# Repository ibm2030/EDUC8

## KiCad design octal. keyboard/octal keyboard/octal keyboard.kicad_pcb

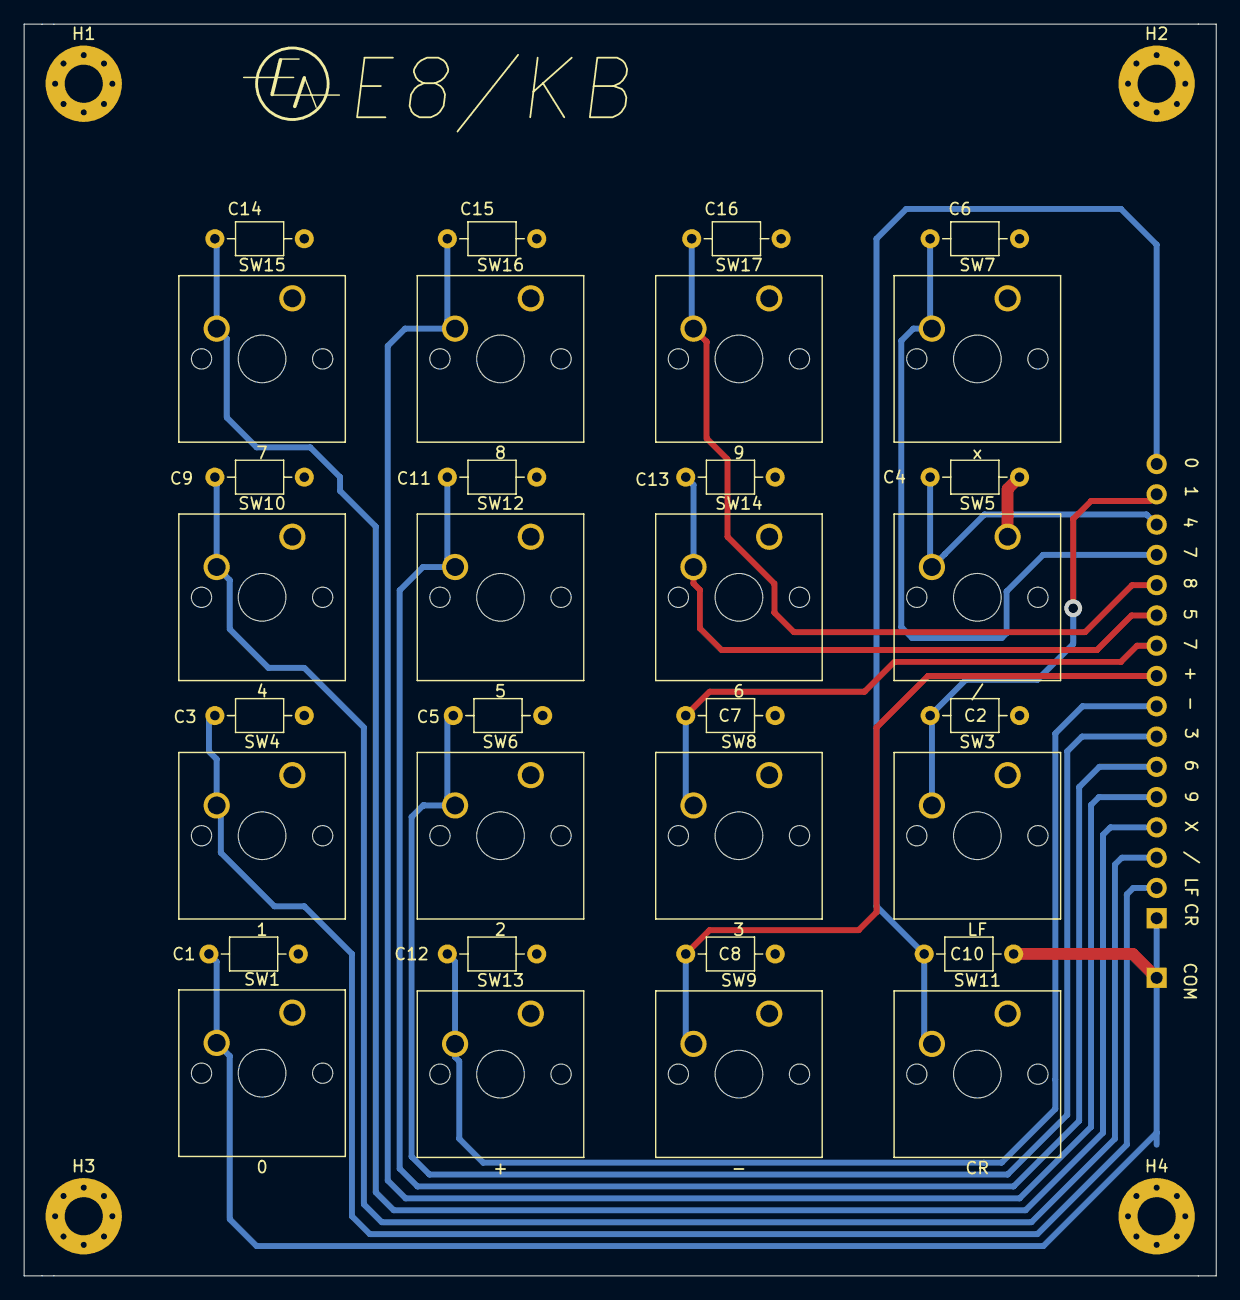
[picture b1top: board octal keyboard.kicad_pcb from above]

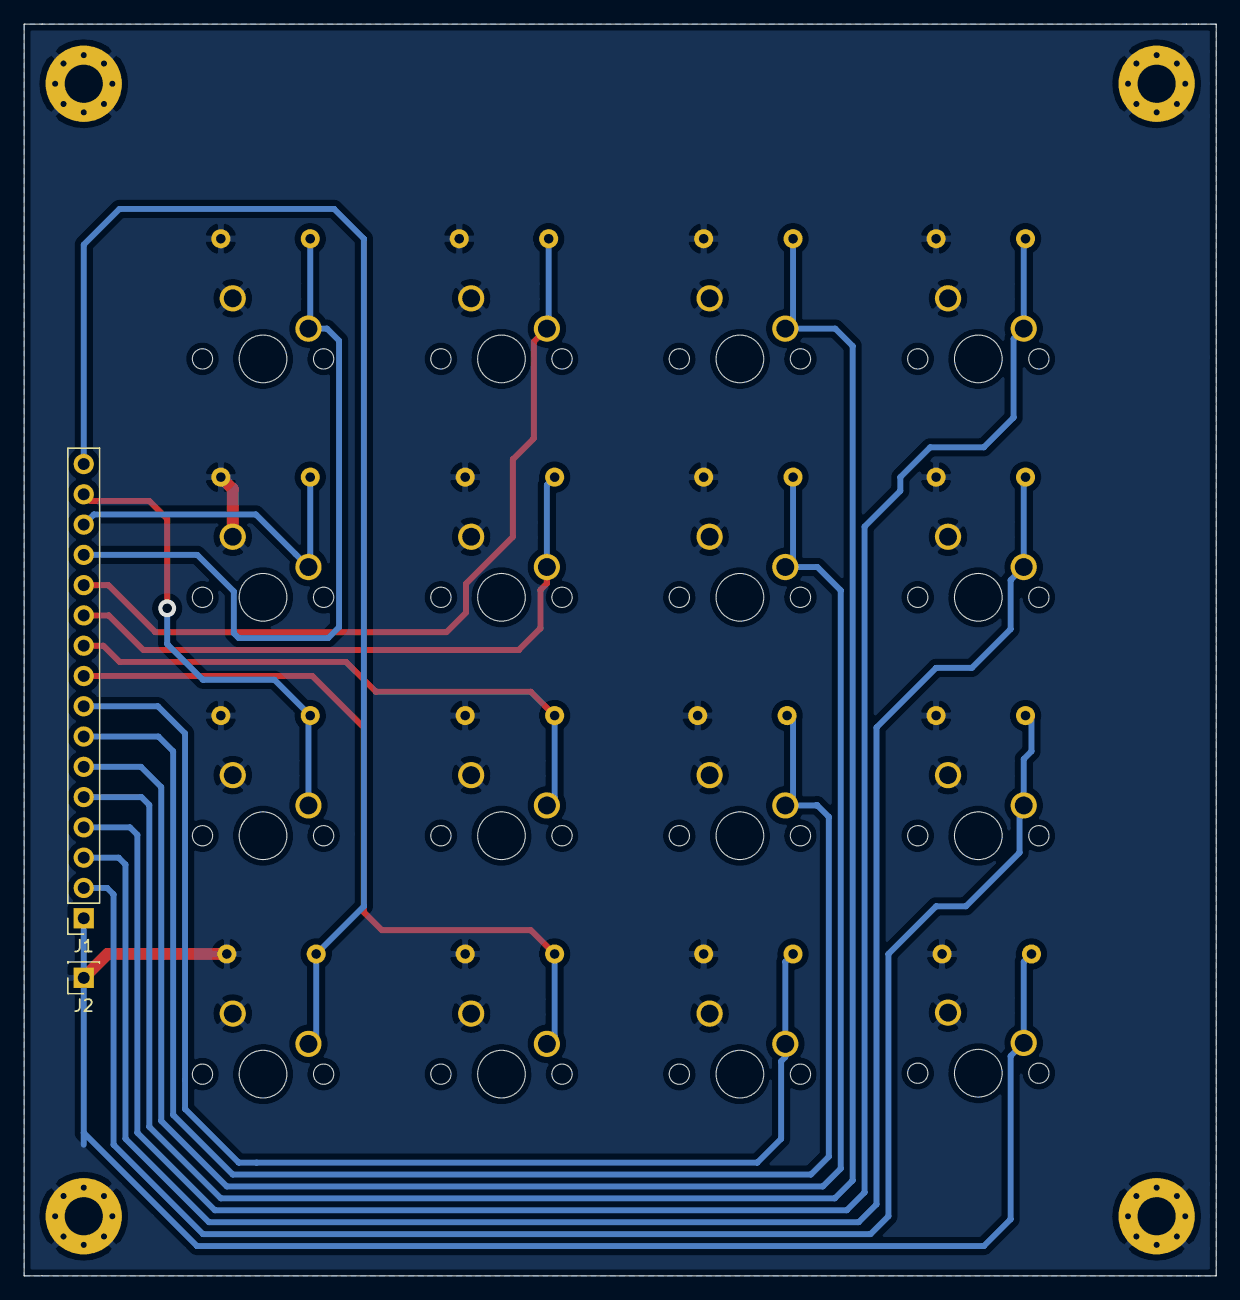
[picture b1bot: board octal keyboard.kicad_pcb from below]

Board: 2 copper layers, 100.0 x 105.0 mm, 38 parts (2 on the bottom side), 17 nets.

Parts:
C1, C3, C4, C5, C6, C7, C8, C9, C10, C11, C12, C13, C14, C15, C16: C_Small; C_Axial_L3.8mm_D2.6mm_P7.50mm_Horizontal
C2: 10nF; C_Axial_L3.8mm_D2.6mm_P7.50mm_Horizontal
H1, H2, H3, H4: MountingHole_Pad; MountingHole_3.2mm_M3_Pad_Via
J1: Conn_01x16_Male; PinSocket_1x16_P2.54mm_Vertical
J2: Conn_01x01_Female; PinSocket_1x01_P2.54mm_Vertical
SW1: 0; SW_Cherry_MX_1.00u_PCB
SW3: LF; SW_Cherry_MX_1.00u_PCB
SW4: 1; SW_Cherry_MX_1.00u_PCB
SW5: /; SW_Cherry_MX_1.00u_PCB
SW6: 2; SW_Cherry_MX_1.00u_PCB
SW7: x; SW_Cherry_MX_1.00u_PCB
SW8: 3; SW_Cherry_MX_1.00u_PCB
SW9: -; SW_Cherry_MX_1.00u_PCB
SW10: 4; SW_Cherry_MX_1.00u_PCB
SW11: CR; SW_Cherry_MX_1.00u_PCB
SW12: 5; SW_Cherry_MX_1.00u_PCB
SW13: +; SW_Cherry_MX_1.00u_PCB
SW14: 6; SW_Cherry_MX_1.00u_PCB
SW15: 7; SW_Cherry_MX_1.00u_PCB
SW16: 8; SW_Cherry_MX_1.00u_PCB
SW17: 9; SW_Cherry_MX_1.00u_PCB

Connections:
0: C1.1, J1.1, SW1.2
1: C3.1, J1.2, SW4.2
2: C5.1, J1.7, SW6.2
3: C7.1, J1.10, SW8.2
4: C9.1, J1.3, SW10.2
5: C11.1, J1.6, SW12.2
6: C13.1, J1.11, SW14.2
7: C14.1, J1.4, SW15.2
8: C15.1, J1.5, SW16.2
9: C16.1, J1.12, SW17.2
+: C12.1, J1.8, SW13.2
-: C8.1, J1.9, SW9.2
COM: C1.2, C2.2, C3.2, C4.2, C5.2, C6.2, C7.2, C8.2, C9.2, C10.2, C11.2, C12.2, C13.2, C14.2, C15.2, C16.2, H1.1, H2.1, H3.1, H4.1, J2.1, SW1.1, SW3.1, SW4.1, SW5.1, SW6.1, SW7.1, SW8.1, SW9.1, SW10.1, SW11.1, SW12.1, SW13.1, SW14.1, SW15.1, SW16.1, SW17.1
CR: C10.1, J1.16, SW11.2
DIV: C4.1, J1.14, SW5.2
LF: C2.1, J1.15, SW3.2
X: C6.1, J1.13, SW7.2

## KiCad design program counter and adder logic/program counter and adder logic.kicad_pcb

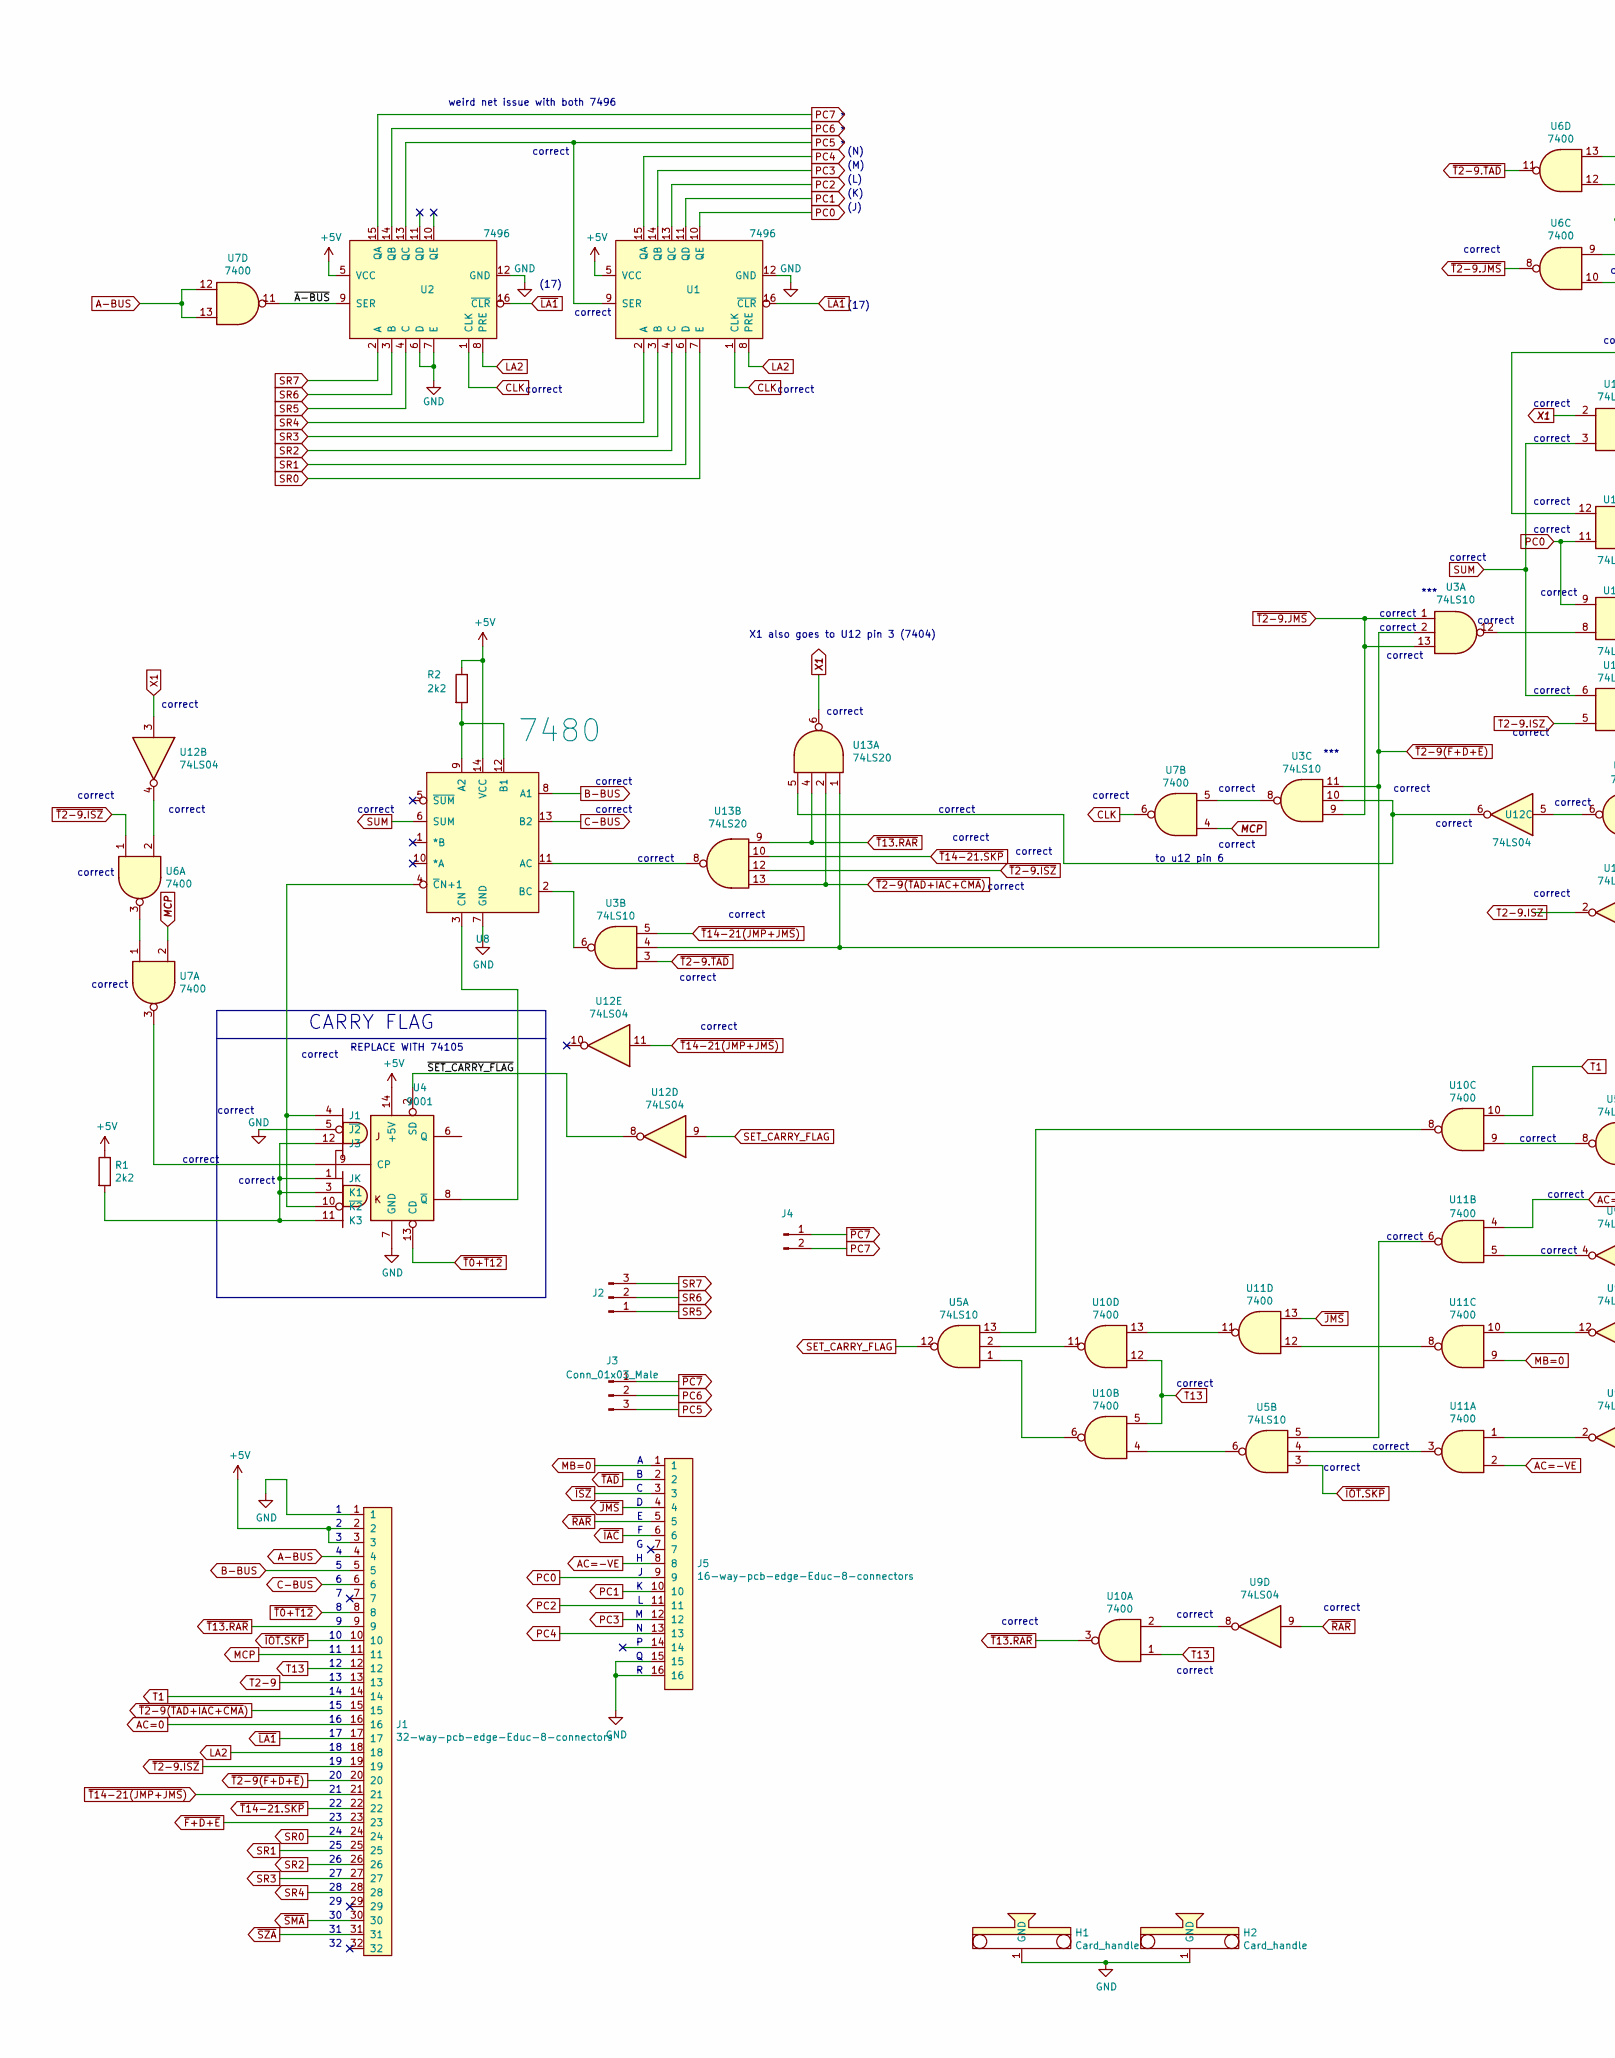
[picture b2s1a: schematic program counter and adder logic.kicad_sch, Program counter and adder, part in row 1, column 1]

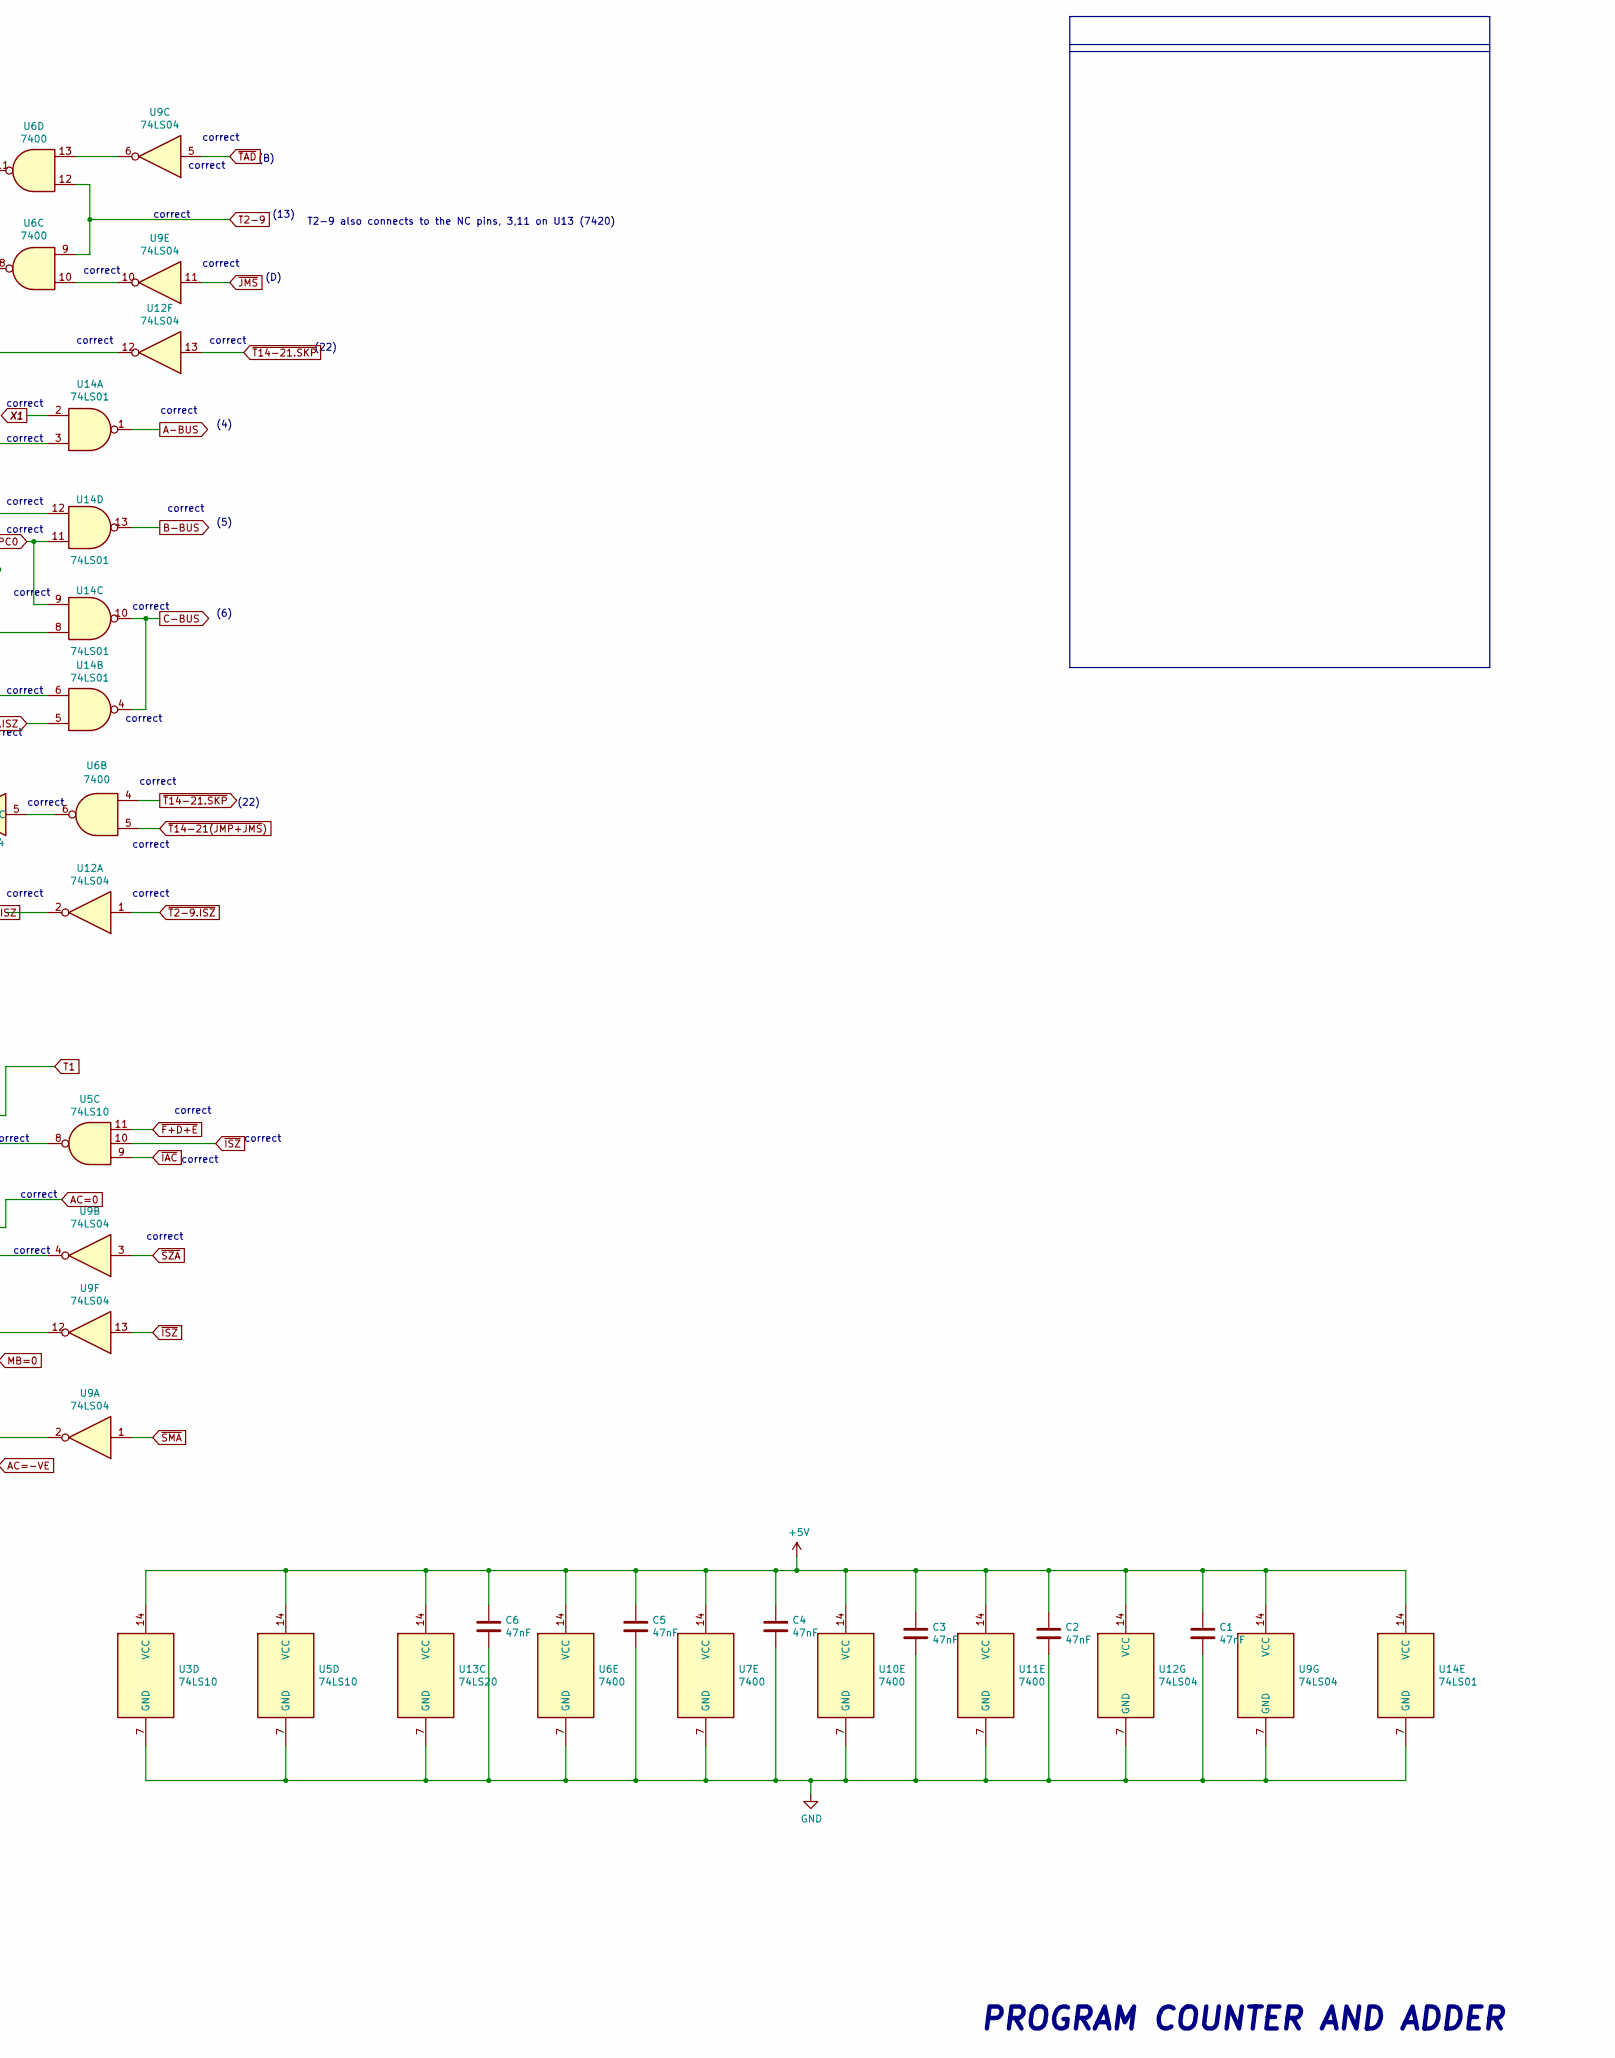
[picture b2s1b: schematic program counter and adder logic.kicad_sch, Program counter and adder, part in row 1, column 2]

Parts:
C1, C2, C3, C4, C5, C6: 47nF; C_Disc_D7.0mm_W2.5mm_P5.00mm
H1, H2: Card_handle
J1: 32-way-pcb-edge-Educ-8-connectors; PCB_32pin
J2, J4: (no value)
J3: Conn_01x03_Male; JST_XH_B3B-XH-AM_1x03_P2.50mm_Vertical
J5: 16-way-pcb-edge-Educ-8-connectors; PCB_16pin
R1, R2: 2k2; R_Axial_DIN0207_L6.3mm_D2.5mm_P10.16mm_Horizontal
U1, U2: 7496; DIP-16_W7.62mm
U3: 74LS10
U4: 9001; DIP-14_W7.62mm
U5: 74LS10; DIP-14_W7.62mm
U6, U7: 7400; DIP-14_W7.62mm
U8: 7480; DIP-14_W7.62mm
U9: 74LS04
U10, U11: 7400
U12: 74LS04; DIP-14_W7.62mm
U13: 74LS20
U14: 74LS01

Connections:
+5V: C1.1, C2.1, C3.1, C4.1, C5.1, C6.1, J1.2, J1.3, R1.1, R2.1, U1.5 (VCC), U2.5 (VCC), U3.14 (VCC), U4.14 (+5V), U5.14 (VCC), U6.14 (VCC), U7.14 (VCC), U8.14 (VCC), U9.14 (VCC), U10.14 (VCC), U11.14 (VCC), U12.14 (VCC), U13.14 (VCC), U14.14 (VCC)
/~A-BUS: U2.9 (SER), U7.11
/~SET_CARRY_FLAG: U4.2 (SD), U12.8
A-BUS: J1.4, U7.12, U7.13, U14.1
AC=0: J1.16, U11.4
AC=-VE: J5.8, U11.2
B-BUS: J1.5, U8.8 (A1), U14.13
C-BUS: J1.6, U8.13 (B2), U14.4, U14.10
CLK: U1.1 (CLK), U2.1 (CLK), U7.6
GND: C1.2, C2.2, C3.2, C4.2, C5.2, C6.2, H1.1 (GND), H2.1 (GND), J1.1, J5.15, J5.16, U1.12 (GND), U2.6 (D), U2.7 (E), U2.12 (GND), U3.7 (GND), U4.5 (~J2), U4.7 (GND), U5.7 (GND), U6.7 (GND), U7.7 (GND), U8.7 (GND), U9.7 (GND), U10.7 (GND), U11.7 (GND), U12.7 (GND), U13.7 (GND), U14.7 (GND)
LA2: J1.18, U1.8 (PRE), U2.8 (PRE)
MB=0: J5.1, U11.9
MCP: J1.11, U7.2, U7.4
unnamed: R1.2, U4.1 (JK), U4.3 (K1), U4.11 (K3), U4.12 (J3)
unnamed: R2.2, U8.9 (A2), U8.12 (B1)
unnamed: U3.6, U8.2 (BC)
unnamed: U3.8, U7.5
unnamed: U4.8 (~Q), U8.3 (CN)
unnamed: U4.9 (CP), U7.3
unnamed: U4.4 (J1), U4.10 (~K2), U8.4 (~CN+1)
unnamed: U6.3, U7.1
unnamed: U6.10, U9.10
unnamed: U6.13, U9.6
unnamed: U9.8, U10.2
unnamed: U5.6, U10.4
unnamed: U5.1, U10.6
unnamed: U5.13, U10.8
unnamed: U5.8, U10.9
unnamed: U5.2, U10.11
unnamed: U10.13, U11.11
unnamed: U9.2, U11.1
unnamed: U5.4, U11.3
unnamed: U9.4, U11.5
unnamed: U5.5, U11.6
unnamed: U9.12, U11.10
unnamed: U11.8, U11.12
unnamed: U6.2, U12.4
unnamed: U6.6, U12.5
unnamed: U3.10, U12.6, U13.5
unnamed: U12.12, U14.12
unnamed: U8.11 (AC), U13.8
unnamed: U3.12, U14.8
PC0: J5.9, U1.10 (QE), U14.9, U14.11
PC1: J5.10, U1.11 (QD)
PC2: J5.11, U1.13 (QC)
PC3: J5.12, U1.14 (QB)
PC4: J5.13, U1.15 (QA)
PC5: J3.3, U1.9 (SER), U2.13 (QC)
PC6: J3.2, U2.14 (QB)
PC7: J4.2, U2.15 (QA)
SET_CARRY_FLAG: U5.12, U12.9
SR0: J1.24, U1.7 (E)
SR1: J1.25, U1.6 (D)
SR2: J1.26, U1.4 (C)
SR3: J1.27, U1.3 (B)
SR4: J1.28, U1.2 (A)
SR5: J2.1, U2.4 (C)
SR6: J2.2, U2.3 (B)
SR7: J2.3, U2.2 (A)
SUM: U8.6 (SUM), U14.3, U14.6
T1: J1.14, U10.10
T2-9: J1.13, U6.9, U6.12
T2-9.ISZ: U12.2, U14.5
T13: J1.12, U10.1, U10.5, U10.12
X1: U12.3, U13.6, U14.2
~F+D+E: J1.23, U5.11
~IAC: J5.6, U5.9
~IOT.SKP: J1.10, U5.3
~ISZ: J5.3, U5.10, U9.13
~JMS: J5.4, U9.11, U11.13
~LA1: J1.17, U1.16 (~CLR), U2.16 (~CLR)
~PC7: J3.1, J4.1
~RAR: J5.5, U9.9
~SMA: J1.30, U9.1
~SZA: J1.31, U9.3
~T0+T12: J1.8, U4.13 (CD)
~T2-9(F+D+E): J1.20, U3.2, U3.4, U3.11, U13.1
~T2-9(TAD+IAC+CMA): J1.15, U13.2, U13.13
~T2-9.ISZ: J1.19, U6.1, U12.1, U13.12
~T2-9.JMS: U3.1, U3.9, U3.13, U6.8
~T2-9.TAD: U3.3, U6.11
~T13.RAR: J1.9, U10.3, U13.4, U13.9
~T14-21(JMP+JMS): J1.21, U3.5, U6.5, U12.11
~T14-21.SKP: J1.22, U6.4, U12.13, U13.10
~TAD: J5.2, U9.5

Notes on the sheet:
correct
correct
(M)
(B)
***
(L)
(22)
(17)
(13)
(6)
CARRY FLAG
(5)
(K)
X1 also goes to U12 pin 3 (7404)
(J)
(N)
(4)
PROGRAM COUNTER AND ADDER
T2-9 also connects to the NC pins, 3,11 on U13 (7420)
REPLACE WITH 74105
weird net issue with both 7496
(D)
to u12 pin 6

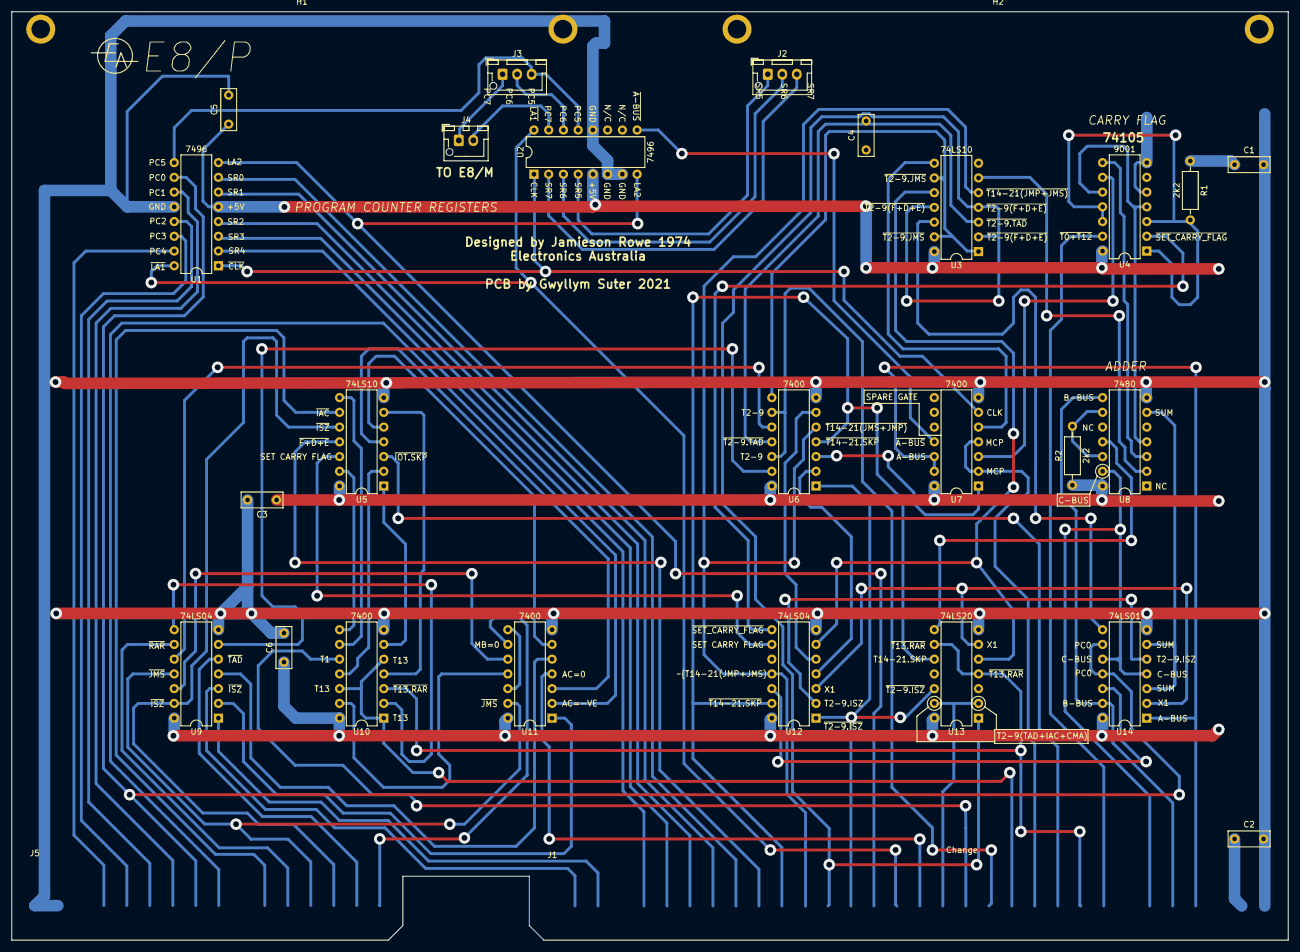
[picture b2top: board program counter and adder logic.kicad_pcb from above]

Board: 2 copper layers, 220.0 x 160.0 mm, 29 parts (0 on the bottom side), 85 nets.
